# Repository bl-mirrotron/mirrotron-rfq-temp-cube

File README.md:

# RFQ Temperature Cube
* <a href="https://github.com/bl-mirrotron/mirrotron-rfq-temp-cube" target="_blank">Source code</a>
* [Cooling system overview](https://docs.bl-mirrotron.com/#cooling-system)
* [Control system overview](https://docs.bl-mirrotron.com/)

The function of the RFQ Temperature Cube is to measure the temperature of the cooling channels on both the upstream and downstream headers. The temperature is measured with <a href="https://www.maximintegrated.com/en/products/sensors/DS18B20.html#:~:text=The%20DS18B20%20communicates%20over%20a,for%20an%20external%20power%20supply." target="_blank">DS18B20</a> One-wire probes connected to a <a href="https://www.pjrc.com/teensy/teensyLC.html" target="_blank">Teensy-LC</a> as the micro-controller. The Teensy-LC communicates to a Blinky-Lite<sup>TM</sup> tray via the <a href="https://github.com/bl-mirrotron/mirrotron-rfq-temp-cube/blob/master/cubeCode/BlinkyBus.h" target="_blank">Blinky-Bus protocol</a> over the Serial1 port.

The schematic for the electrical circuit is shown in Figure 1. The board is designed to handle up to eight probes with each probe having it's own on/off power control if a individual channel needs a reboot. The PCB layout for the electrical circuit is shown in Figure 2. There is a 2x20 pin header mounted on the back of the PCB so that the cube can be directly mounted to a Raspberry Pi header for power and communications. 5V power to the Teensy-LC is provided through the header from Raspberry Pi. A manufactured board is shown in Figure 3.

<p style="text-align:center;font-size: large;"><span style="font-weight: bold;color: green;">Figure 1. </span> <span style="font-style: italic;">Electrical Schematic for rfq-temp-cube board</span></p>
<div style="width:100%;text-align:center;"></div><br>

<p style="text-align:center;font-size: large;"><span style="font-weight: bold;color: green;">Figure 2. </span> <span style="font-style: italic;">PCB layout for rfq-temp-cube board</span></p>
<div style="width:100%;text-align:center;"></div><br>

<p style="text-align:center;font-size: large;"><span style="font-weight: bold;color: green;">Figure 3. </span> <span style="font-style: italic;">rfq-temp-cube</span></p>
<div style="width:100%;text-align:center;"></div><br>

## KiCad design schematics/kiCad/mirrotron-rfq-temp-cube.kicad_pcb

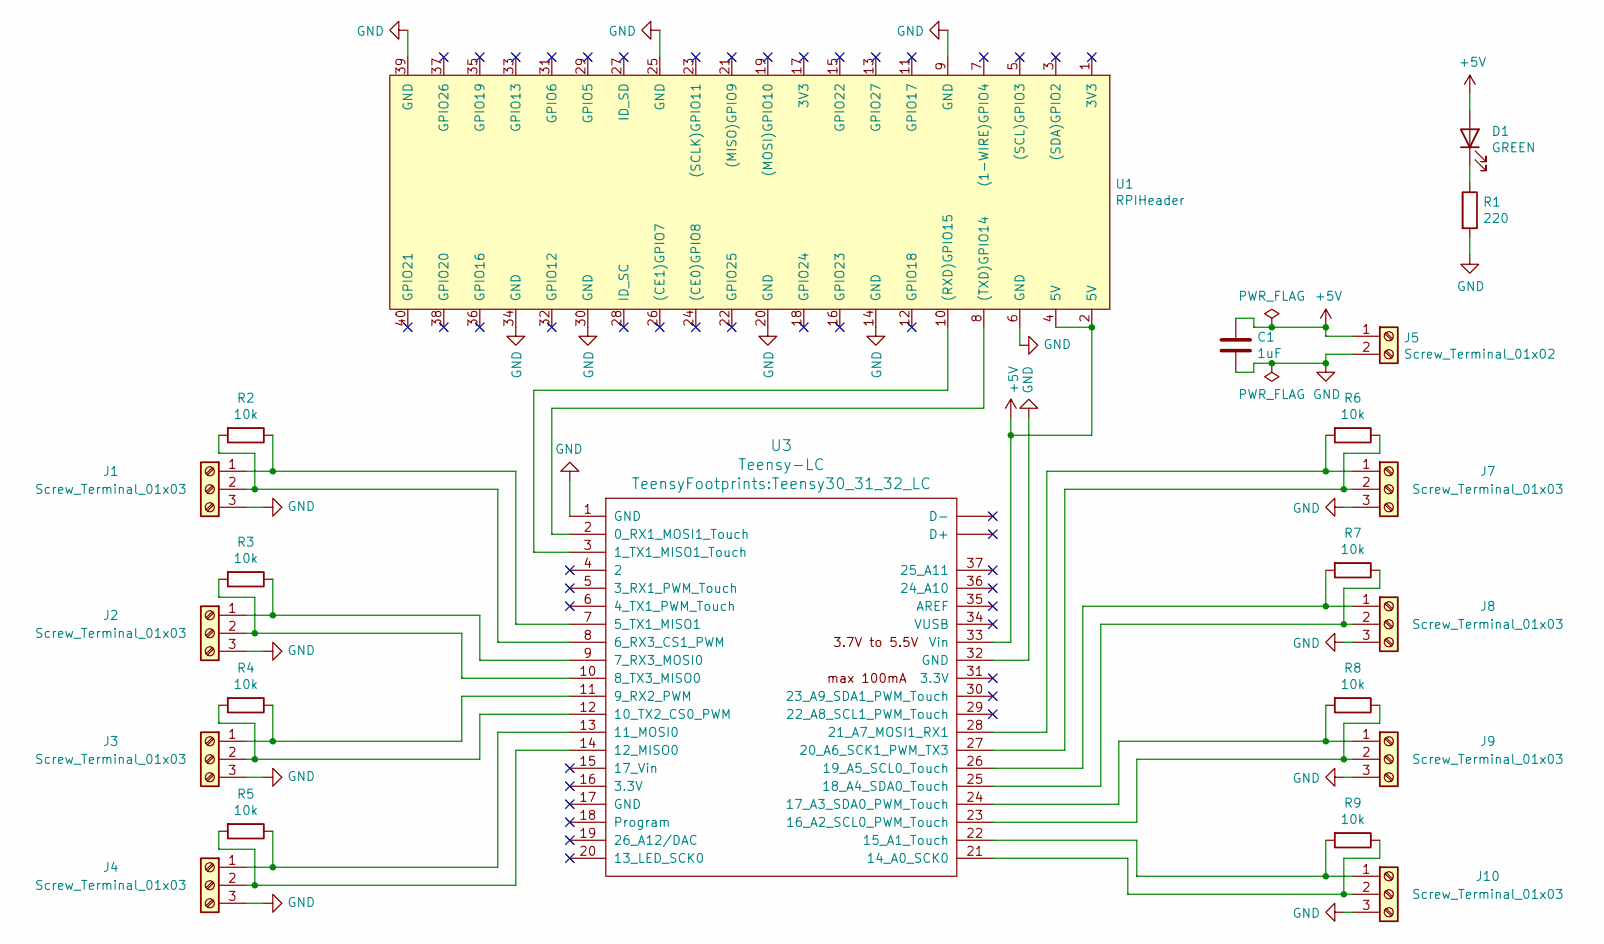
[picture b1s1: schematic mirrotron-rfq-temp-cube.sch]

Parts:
C1: 1uF; C_1206_3216Metric_Pad1.33x1.80mm_HandSolder
D1: GREEN; LED_D5.0mm
J1, J2, J3, J4, J7, J8, J9, J10: Screw_Terminal_01x03; TerminalBlock_bornier-3_P5.08mm
J5: Screw_Terminal_01x02; TerminalBlock_bornier-2_P5.08mm
R1: 220; R_1206_3216Metric_Pad1.42x1.75mm_HandSolder
R2, R3, R4, R5, R6, R7, R8, R9: 10k; R_1206_3216Metric_Pad1.42x1.75mm_HandSolder
U1: RPIHeader; PinHeader_2x20_P2.54mm_Vertical
U3: Teensy-LC; Teensy30_31_32_LC

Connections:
+5V: C1.1, D1.2 (A), J5.1, U1.2 (5V), U1.4 (5V), U3.33 (Vin)
GND: C1.2, J1.3, J2.3, J3.3, J4.3, J5.2, J7.3, J8.3, J9.3, J10.3, R1.2, U1.6 (GND), U1.9 (GND), U1.14 (GND), U1.20 (GND), U1.25 (GND), U1.30 (GND), U1.34 (GND), U1.39 (GND), U3.1 (GND), U3.32 (GND)
unnamed: D1.1 (K), R1.1
unnamed: J1.1, R2.1, U3.7 (5_TX1_MISO1)
unnamed: J1.2, R2.2, U3.8 (6_RX3_CS1_PWM)
unnamed: J2.1, R3.1, U3.9 (7_RX3_MOSI0)
unnamed: J2.2, R3.2, U3.10 (8_TX3_MISO0)
unnamed: J3.1, R4.1, U3.11 (9_RX2_PWM)
unnamed: J3.2, R4.2, U3.12 (10_TX2_CS0_PWM)
unnamed: J4.1, R5.1, U3.13 (11_MOSI0)
unnamed: J4.2, R5.2, U3.14 (12_MISO0)
unnamed: J7.1, R6.2, U3.28 (21_A7_MOSI1_RX1)
unnamed: J7.2, R6.1, U3.27 (20_A6_SCK1_PWM_TX3)
unnamed: J8.1, R7.2, U3.26 (19_A5_SCL0_Touch)
unnamed: J8.2, R7.1, U3.25 (18_A4_SDA0_Touch)
unnamed: J9.1, R8.2, U3.24 (17_A3_SDA0_PWM_Touch)
unnamed: J9.2, R8.1, U3.23 (16_A2_SCL0_PWM_Touch)
unnamed: J10.1, R9.2, U3.22 (15_A1_Touch)
unnamed: J10.2, R9.1, U3.21 (14_A0_SCK0)
unnamed: U1.8 ((TXD)GPIO14), U3.2 (0_RX1_MOSI1_Touch)
unnamed: U1.10 ((RXD)GPIO15), U3.3 (1_TX1_MISO1_Touch)

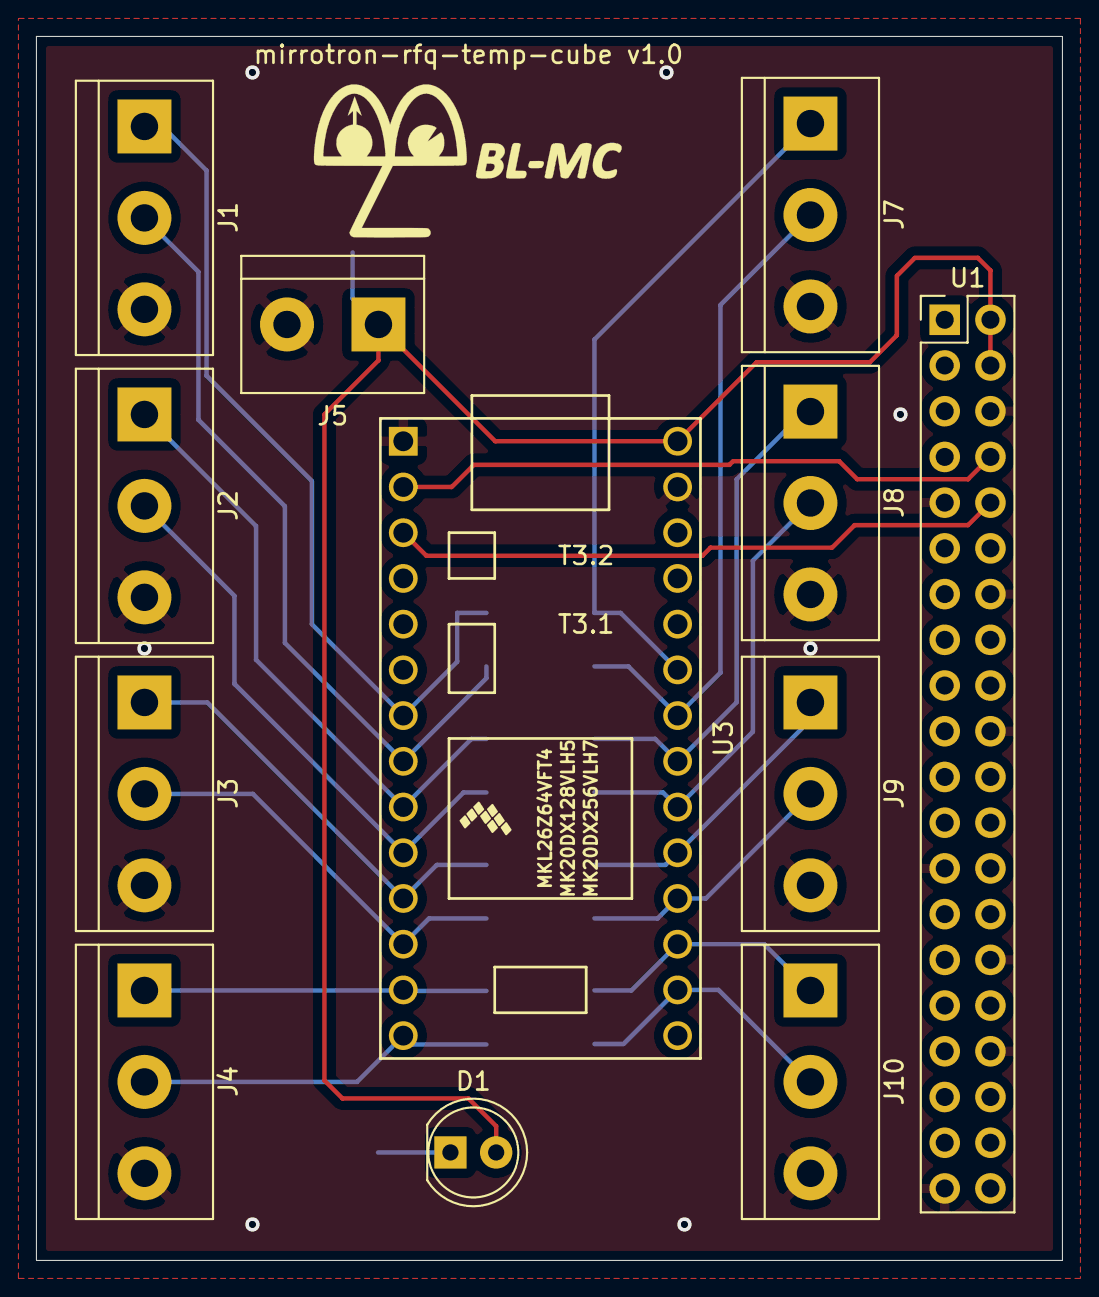
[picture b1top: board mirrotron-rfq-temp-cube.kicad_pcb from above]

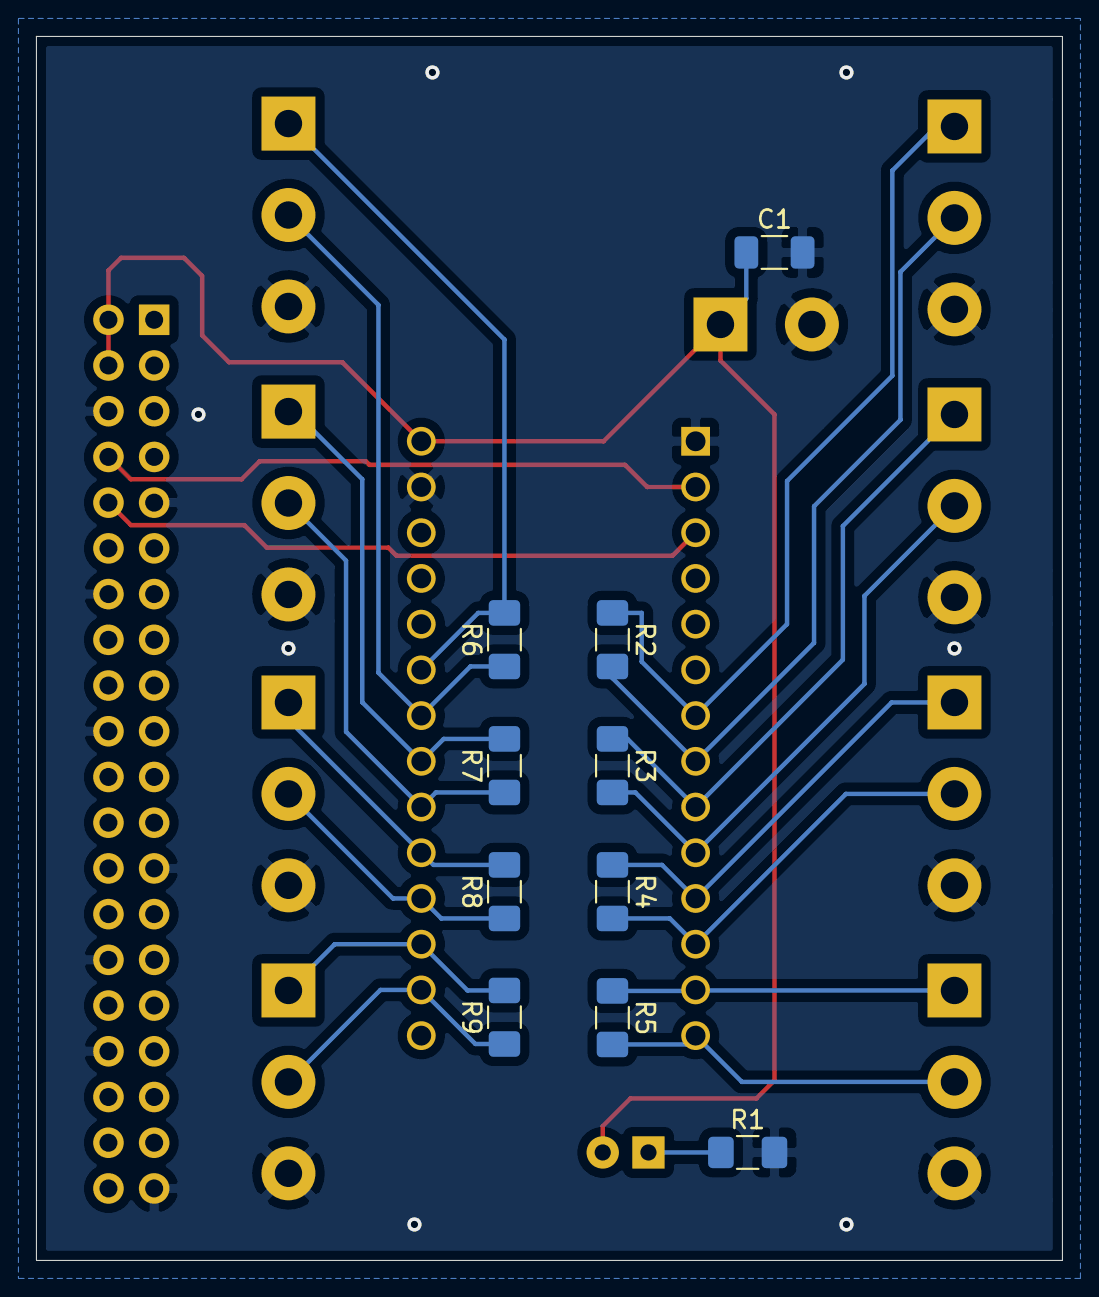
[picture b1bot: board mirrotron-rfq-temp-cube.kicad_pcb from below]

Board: 2 copper layers, 57.0 x 68.0 mm, 22 parts (10 on the bottom side), 21 nets.

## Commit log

2022-03-30 circuit board desgined
2022-04-07 cube code working
2022-04-13 updated on off for ds18b20
2022-08-05 added doc
2022-08-06 Added cube pics
2022-08-11 Set theme jekyll-theme-tactile
